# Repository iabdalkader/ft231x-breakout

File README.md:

ft231x-breakout
===============

FT231X Breakout Board

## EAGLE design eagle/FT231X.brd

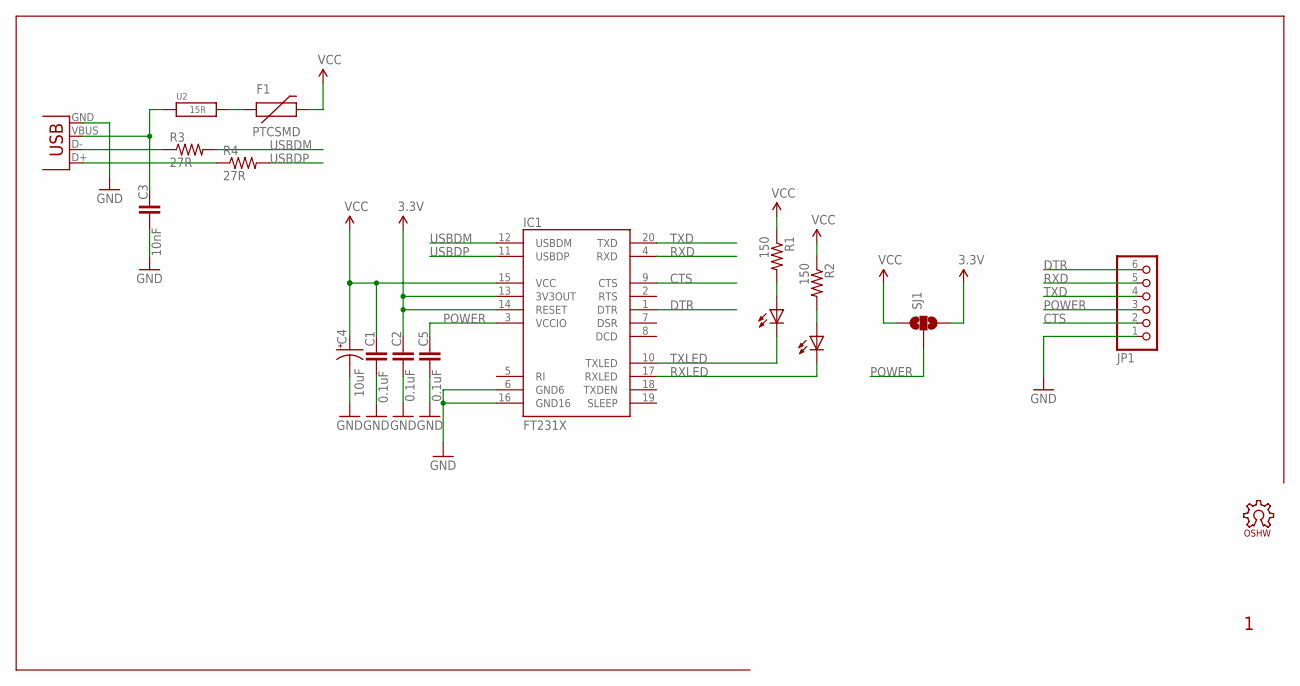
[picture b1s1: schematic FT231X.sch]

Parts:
C1, C2, C5: 0.1uF; 0402-CAP
C3: 10nF; 0402-CAP
C4: 10uF; EIA3216
D1, D2: LED0603; LED-0603
F1: PTCSMD; PTC-1206
IC1: FT231X; SSOP20
JP1: PINHD-1X6; 1X06
LOGO1: OSHW_LOGO_FILLX0100-NT; OSHW_FILLX100_NOTEXT
R1, R2: 150; 0402-RES
R3, R4: 27R; 0402-RES
SJ1: SOLDERJUMPER_2WAYS; SJ_3
U2: 15R; 0402-CAP
X1: USBSMD; USB-MINIB

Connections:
3.3V: C2.1, IC1.13 (3V3OUT), IC1.14 (RESET), SJ1.3
CTS: IC1.9 (CTS), JP1.2
DTR: IC1.1 (DTR), JP1.6
GND: C1.2, C2.2, C3.2, C4.C (-), C5.2, IC1.6 (GND6), IC1.16 (GND16), JP1.1, X1.GND
unnamed: D2.A, R1.2
unnamed: R3.1, X1.D-
unnamed: R4.1, X1.D+
unnamed: F1.1, U2.2
unnamed: D1.A, R2.2
POWER: C5.1, IC1.3 (VCCIO), JP1.3, SJ1.2
RXD: IC1.4 (RXD), JP1.5
RXLED: D1.C, IC1.17 (RXLED)
TXD: IC1.20 (TXD), JP1.4
TXLED: D2.C, IC1.10 (TXLED)
USBDM: IC1.12 (USBDM), R3.2
USBDP: IC1.11 (USBDP), R4.2
VBUS: C3.1, U2.1, X1.VBUS
VCC: C1.1, C4.A (+), F1.2, IC1.15 (VCC), R1.1, R2.1, SJ1.1

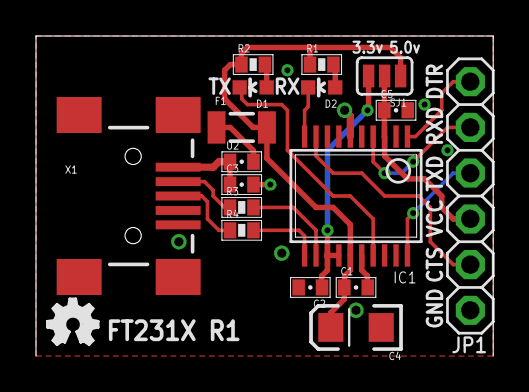
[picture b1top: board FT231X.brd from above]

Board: 2 copper layers, 25.4 x 17.8 mm, 18 parts (0 on the bottom side), 18 nets.

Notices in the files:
eagle/FT231X.brd:
Copyright (c) 2013 Ibrahim Abd Elkader
This work is licensed under the Creative Commons Attribution-ShareAlike 3.0 License.
To view a copy of this license, visit http://creativecommons.org/licenses/by-sa/3.0
